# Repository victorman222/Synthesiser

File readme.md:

Eurorack compatible synthesiser module schematics and pcb's

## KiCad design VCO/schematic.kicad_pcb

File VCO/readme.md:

Voltage controlled oscillator built with CD4069 hex-inverter IC and with discrete transistor exponential converter. 

Features: 

Exponential 1v/Oct tracking

Sawtooth and Pulse output

Pulsewidth modulation.

Low cost (only one IC)

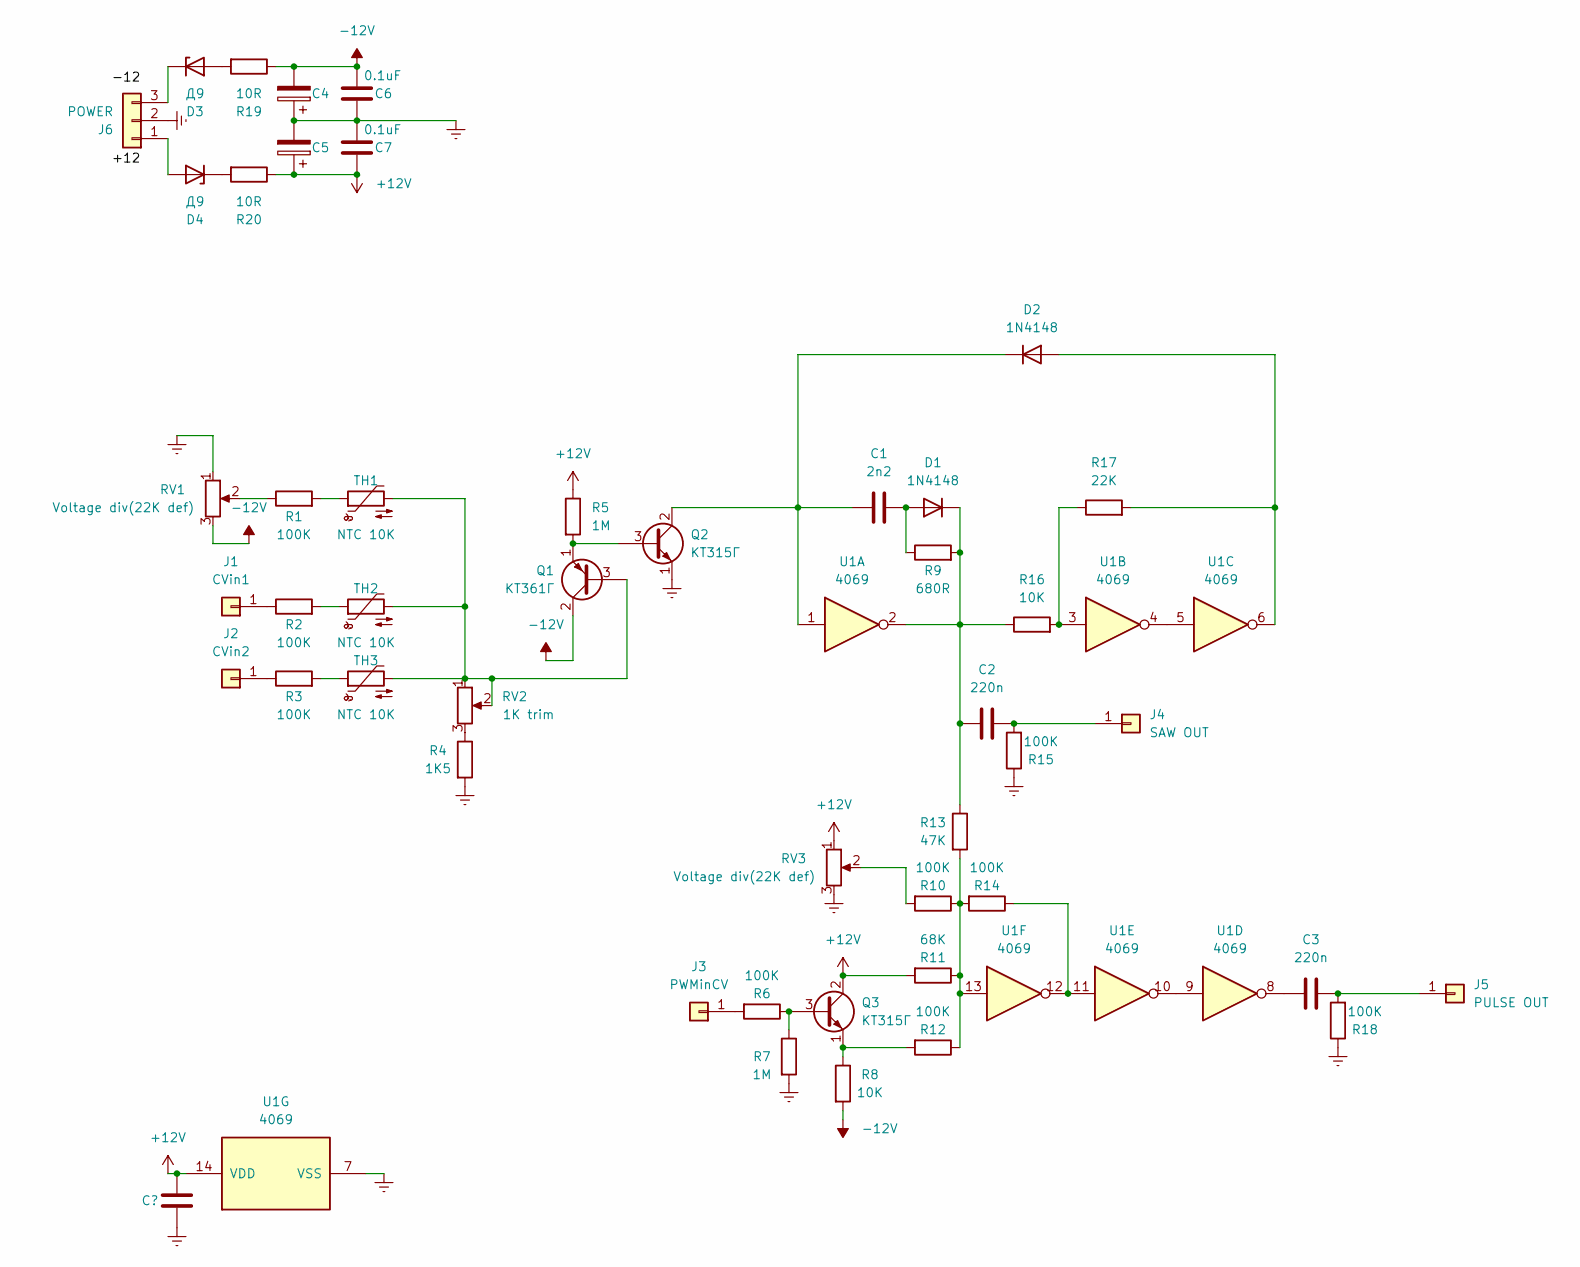
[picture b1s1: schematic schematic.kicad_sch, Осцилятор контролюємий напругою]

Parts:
C1: 2n2; C_Disc_D7.5mm_W5.0mm_P10.00mm
C2, C3: 220n; C_Rect_L11.0mm_W5.1mm_P10.00mm_MKT
C4, C5: (no value)
C6, C7: 0.1uF; C_Disc_D7.5mm_W5.0mm_P10.00mm
D1, D2: 1N4148; D_DO-35_SOD27_P2.54mm_Vertical_KathodeUp
D3, D4: Д9; D_DO-41_SOD81_P7.62mm_Horizontal
J1: CVin1; PinHeader_1x01_P2.54mm_Vertical
J2: CVin2; PinHeader_1x01_P2.54mm_Vertical
J3: PWMinCV; PinHeader_1x01_P2.54mm_Vertical
J4: SAW OUT; PinHeader_1x01_P2.54mm_Vertical
J5: PULSE OUT; PinHeader_1x01_P2.54mm_Vertical
J6: POWER; PinHeader_1x03_P2.54mm_Vertical
Q1: КТ361Г; PinHeader_1x03_P2.54mm_Vertical
Q2, Q3: КТ315Г; PinHeader_1x03_P2.54mm_Vertical
R1, R2, R3, R6, R10, R12, R14: 100K; R_Axial_DIN0207_L6.3mm_D2.5mm_P2.54mm_Vertical
R4: 1K5; R_Axial_DIN0207_L6.3mm_D2.5mm_P2.54mm_Vertical
R5, R7: 1M; R_Axial_DIN0207_L6.3mm_D2.5mm_P2.54mm_Vertical
R8, R16: 10K; R_Axial_DIN0207_L6.3mm_D2.5mm_P2.54mm_Vertical
R9: 680R; R_Axial_DIN0207_L6.3mm_D2.5mm_P2.54mm_Vertical
R11: 68K; R_Axial_DIN0207_L6.3mm_D2.5mm_P2.54mm_Vertical
R13: 47K; R_Axial_DIN0207_L6.3mm_D2.5mm_P2.54mm_Vertical
R15, R18: 100K; R_Axial_DIN0207_L6.3mm_D2.5mm_P5.08mm_Vertical
R17: 22K; R_Axial_DIN0207_L6.3mm_D2.5mm_P5.08mm_Vertical
R19, R20: 10R; R_Axial_DIN0204_L3.6mm_D1.6mm_P5.08mm_Vertical
RV1, RV3: Voltage div(22K def); PinSocket_1x03_P2.54mm_Vertical
RV2: 1K trim; SP5-2
TH1, TH2, TH3: NTC 10K; R_Axial_DIN0204_L3.6mm_D1.6mm_P5.08mm_Horizontal
U1: 4069; DIP-14_W7.62mm_Socket_LongPads

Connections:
+12V: C5.1, C7.1, Q3.2 (C), R5.1, R11.2, R20.1, RV3.1, U1.14 (VDD)
-12V: C4.2, C6.2, Q1.2 (C), R8.2, R19.1, RV1.3
Earth: C4.1, C5.2, C6.1, C7.2, J6.2, Q2.1 (E), R4.2, R7.2, R15.1, R18.1, RV1.1, RV3.3, U1.7 (VSS)
unnamed: C1.1, D2.1 (K), Q2.2 (C), U1.1
unnamed: C1.2, D1.2 (A), R9.1
unnamed: C2.1, D1.1 (K), R9.2, R13.1, R16.1, U1.2
unnamed: C2.2, J4.1, R15.2
unnamed: C3.1, U1.8
unnamed: C3.2, J5.1, R18.2
unnamed: D2.2 (A), R17.2, U1.6
unnamed: D3.1 (K), J6.3
unnamed: D3.2 (A), R19.2
unnamed: D4.1 (K), R20.2
unnamed: D4.2 (A), J6.1
unnamed: J1.1, R2.1
unnamed: J2.1, R3.1
unnamed: J3.1, R6.2
unnamed: Q1.1 (E), Q2.3 (B), R5.2
unnamed: Q1.3 (B), RV2.1, RV2.2, TH1.2, TH2.2, TH3.2
unnamed: Q3.1 (E), R8.1, R12.2
unnamed: Q3.3 (B), R6.1, R7.1
unnamed: R1.1, RV1.2
unnamed: R1.2, TH1.1
unnamed: R2.2, TH2.1
unnamed: R3.2, TH3.1
unnamed: R4.1, RV2.3
unnamed: R10.1, R11.1, R12.1, R13.2, R14.2, U1.13
unnamed: R10.2, RV3.2
unnamed: R14.1, U1.11, U1.12
unnamed: R16.2, R17.1, U1.3
unnamed: U1.4, U1.5
unnamed: U1.9, U1.10

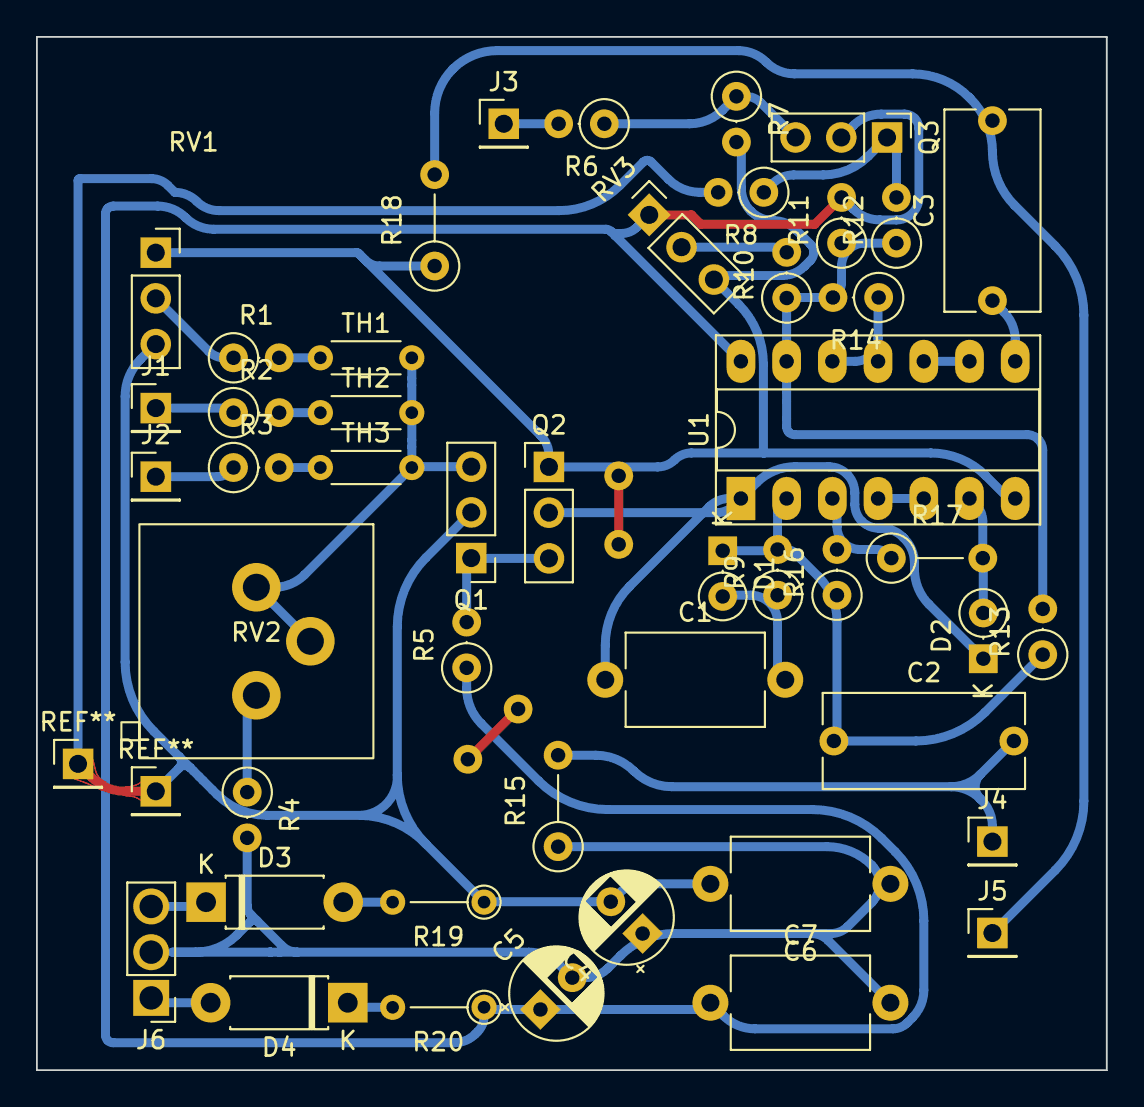
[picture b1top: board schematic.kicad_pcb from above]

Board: 2 copper layers, 59.4 x 57.4 mm, 47 parts (0 on the bottom side), 32 nets.

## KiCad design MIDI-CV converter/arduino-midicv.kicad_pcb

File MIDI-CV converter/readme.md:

MIDI-CV converter using arduino mega 2560

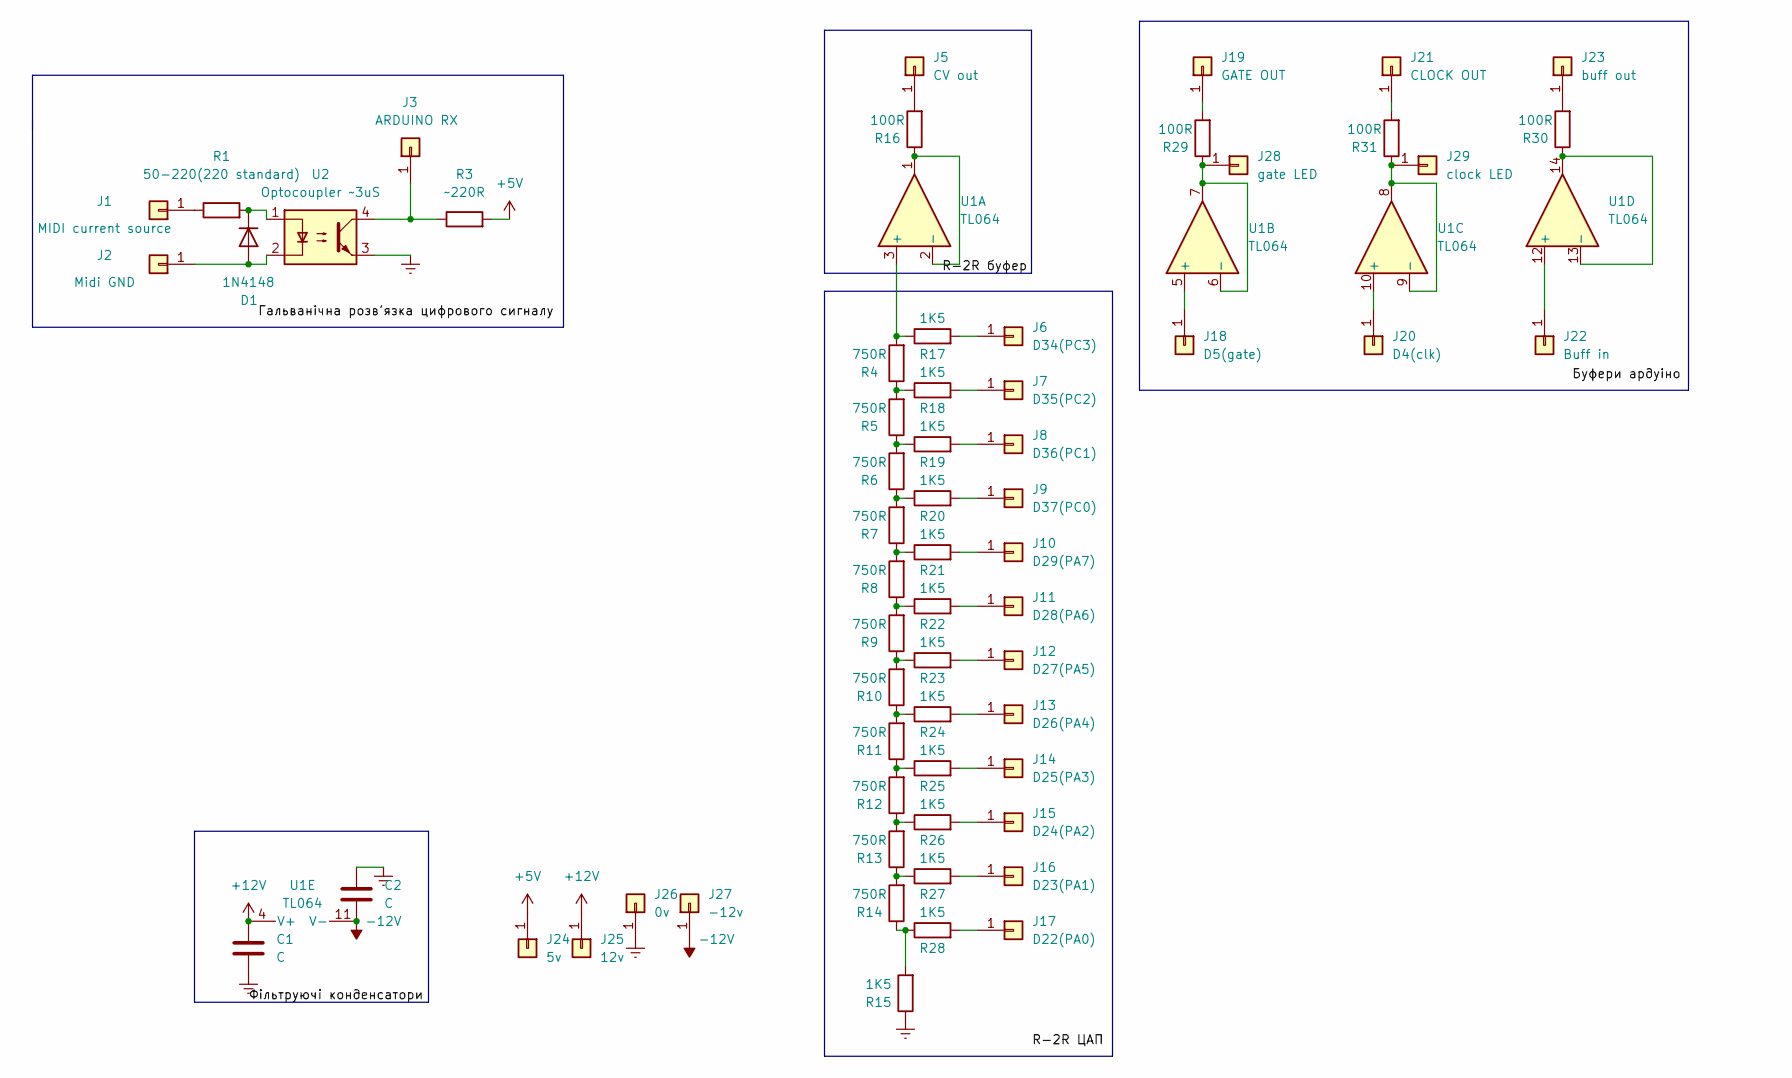
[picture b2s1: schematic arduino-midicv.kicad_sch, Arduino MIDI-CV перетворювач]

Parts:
C1, C2: C; C_Disc_D7.5mm_W4.4mm_P5.00mm
D1: 1N4148; D_DO-35_SOD27_P3.81mm_Vertical_AnodeUp
J1: MIDI current source; PinHeader_1x01_P2.54mm_Vertical
J2: Midi GND; PinHeader_1x01_P2.54mm_Vertical
J3: ARDUINO RX; PinHeader_1x01_P2.54mm_Vertical
J5: CV out; PinHeader_1x01_P2.54mm_Vertical
J6: D34(PC3); PinHeader_1x01_P2.54mm_Vertical
J7: D35(PC2); PinHeader_1x01_P2.54mm_Vertical
J8: D36(PC1); PinHeader_1x01_P2.54mm_Vertical
J9: D37(PC0); PinHeader_1x01_P2.54mm_Vertical
J10: D29(PA7); PinHeader_1x01_P2.54mm_Vertical
J11: D28(PA6); PinHeader_1x01_P2.54mm_Vertical
J12: D27(PA5); PinHeader_1x01_P2.54mm_Vertical
J13: D26(PA4); PinHeader_1x01_P2.54mm_Vertical
J14: D25(PA3); PinHeader_1x01_P2.54mm_Vertical
J15: D24(PA2); PinHeader_1x01_P2.54mm_Vertical
J16: D23(PA1); PinHeader_1x01_P2.54mm_Vertical
J17: D22(PA0); PinHeader_1x01_P2.54mm_Vertical
J18: D5(gate); PinHeader_1x01_P2.54mm_Vertical
J19: GATE OUT; PinHeader_1x01_P2.54mm_Vertical
J20: D4(clk); PinHeader_1x01_P2.54mm_Vertical
J21: CLOCK OUT; PinHeader_1x01_P2.54mm_Vertical
J22: Buff in; PinHeader_1x01_P2.54mm_Vertical
J23: buff out; PinHeader_1x01_P2.54mm_Vertical
J24: 5v; PinHeader_1x01_P2.54mm_Vertical
J25: 12v; PinHeader_1x01_P2.54mm_Vertical
J26: 0v; PinHeader_1x01_P2.54mm_Vertical
J27: -12v; PinHeader_1x01_P2.54mm_Vertical
J28: gate LED; PinHeader_1x01_P2.54mm_Vertical
J29: clock LED; PinHeader_1x01_P2.54mm_Vertical
R1: 50-220(220 standard); R_Axial_DIN0309_L9.0mm_D3.2mm_P5.08mm_Vertical
R3: ~220R; R_Axial_DIN0309_L9.0mm_D3.2mm_P5.08mm_Vertical
R4, R5, R6, R7, R8, R9, R10, R11, R12, R13, R14: 750R; R_Axial_DIN0309_L9.0mm_D3.2mm_P12.70mm_Horizontal
R15, R17, R18, R19, R20, R21, R22, R23, R24, R25, R26, R27, R28: 1K5; R_Axial_DIN0309_L9.0mm_D3.2mm_P12.70mm_Horizontal
R16, R29, R30, R31: 100R; R_Axial_DIN0309_L9.0mm_D3.2mm_P2.54mm_Vertical
U1: TL064; DIP-14_W7.62mm
U2: Optocoupler ~3uS; DIP-4_W7.62mm

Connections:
+5V: J24.1, R3.2
+12V: C1.2, J25.1, U1.4 (V+)
-12V: C2.1, J27.1, U1.11 (V-)
Earth: C1.1, C2.2, J26.1, R15.1, U2.3
unnamed: D1.1 (K), R1.2, U2.1
unnamed: D1.2 (A), J2.1, U2.2
unnamed: J1.1, R1.1
unnamed: J3.1, R3.1, U2.4
unnamed: J5.1, R16.2
unnamed: J6.1, R17.2
unnamed: J7.1, R18.2
unnamed: J8.1, R19.2
unnamed: J9.1, R20.2
unnamed: J10.1, R21.2
unnamed: J11.1, R22.2
unnamed: J12.1, R23.2
unnamed: J13.1, R24.2
unnamed: J14.1, R25.2
unnamed: J15.1, R26.2
unnamed: J16.1, R27.2
unnamed: J17.1, R28.2
unnamed: J18.1, U1.5 (+)
unnamed: J19.1, R29.2
unnamed: J20.1, U1.10 (+)
unnamed: J21.1, R31.2
unnamed: J22.1, U1.12 (+)
unnamed: J23.1, R30.2
unnamed: R10.1, R11.2, R24.1
unnamed: R9.1, R10.2, R23.1
unnamed: R11.1, R12.2, R25.1
unnamed: R12.1, R13.2, R26.1
unnamed: R13.1, R14.2, R27.1
unnamed: R14.1, R15.2, R28.1
unnamed: R16.1, U1.1, U1.2 (-)
unnamed: R4.2, R17.1, U1.3 (+)
unnamed: R4.1, R5.2, R18.1
unnamed: R5.1, R6.2, R19.1
unnamed: R6.1, R7.2, R20.1
unnamed: R7.1, R8.2, R21.1
unnamed: R8.1, R9.2, R22.1
unnamed: J28.1, R29.1, U1.6 (-), U1.7
unnamed: J29.1, R31.1, U1.8, U1.9 (-)
unnamed: R30.1, U1.13 (-), U1.14

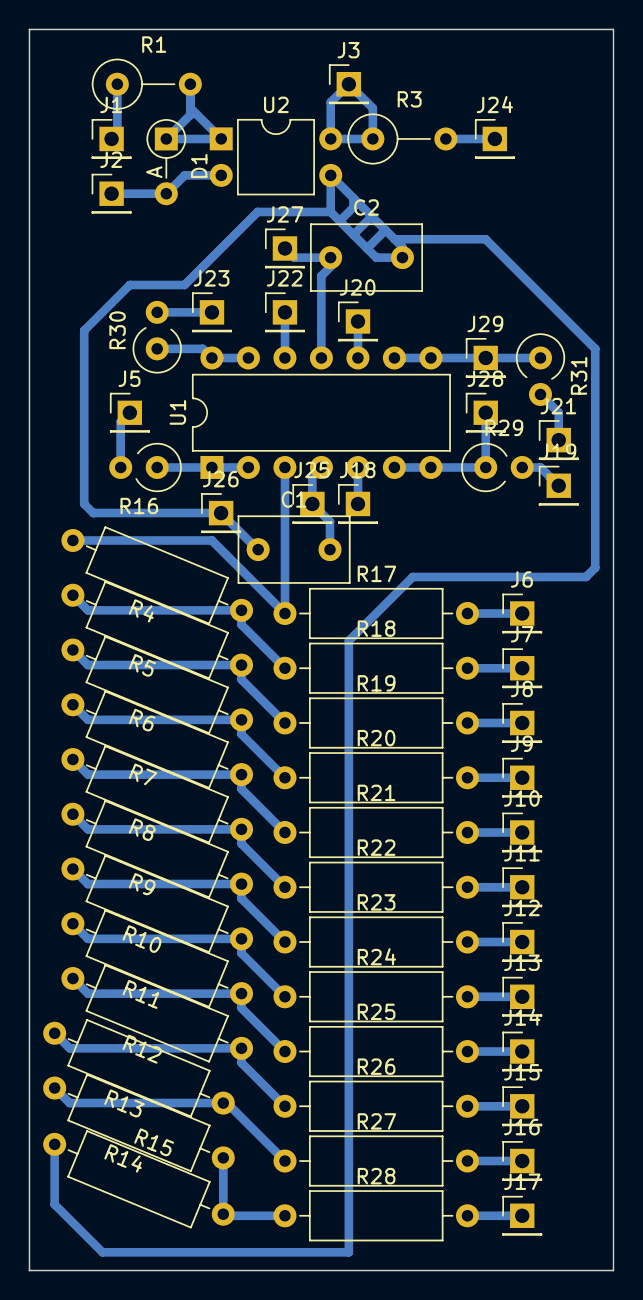
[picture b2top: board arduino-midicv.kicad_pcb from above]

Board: 2 copper layers, 40.6 x 86.4 mm, 63 parts (0 on the bottom side), 43 nets.

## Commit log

2022-09-29 Create recipe_how_to_cook_victore
2022-09-29 Rename midicv.ino to code.ino
